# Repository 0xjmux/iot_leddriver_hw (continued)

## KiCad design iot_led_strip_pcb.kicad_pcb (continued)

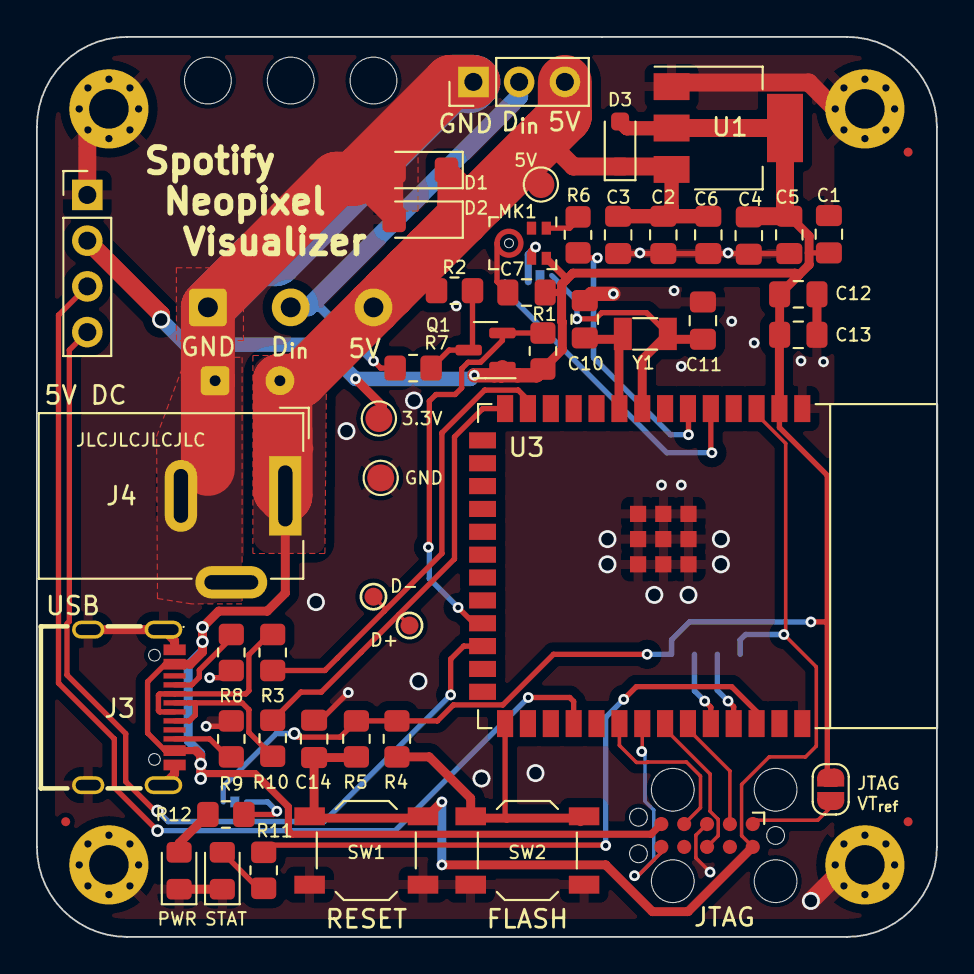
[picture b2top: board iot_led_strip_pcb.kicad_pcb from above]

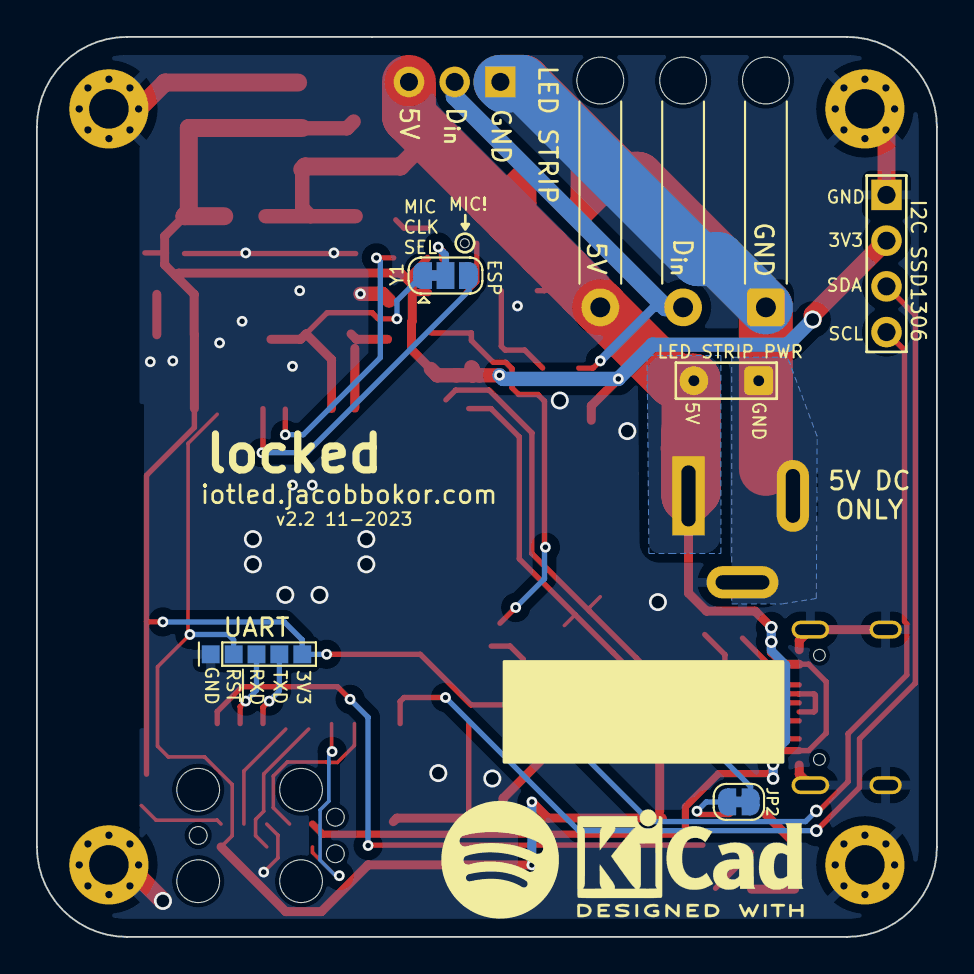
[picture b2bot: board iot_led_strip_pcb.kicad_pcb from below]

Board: 2 copper layers, 50.0 x 50.0 mm, 59 parts (4 on the bottom side), 33 nets.

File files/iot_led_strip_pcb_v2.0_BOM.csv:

"Source:","/home/jmux/Github/spotify-iot-led-driver/iot_leddriver_hw/iot_led_strip_pcb.kicad_sch"
"Date:","Sun 17 Sep 2023 01:23:37 PM PDT"
"Tool:","Eeschema 7.0.6-1.fc37"
"Generator:","/usr/share/kicad/plugins/bom_csv_grouped_by_value.py"
"Component Count:","38"

"Collated Components:"

"Item","Qty","Reference(s)","Value","LibPart","Footprint","Datasheet","DNP","LCSC","Sim.Device","Sim.Params","Sim.Pins","Sim.Type","Vendor"
"1","6","C1, C2, C3, C5, C7, C13","10uF","Device:C","Capacitor_SMD:C_0805_2012Metric_Pad1.18x1.45mm_HandSolder","~","","C15850","","","","","https://www.lcsc.com/product-detail/Multilayer-Ceramic-Capac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"
"2","3","C4, C6, C12","100nF","Device:C","Capacitor_SMD:C_0805_2012Metric_Pad1.18x1.45mm_HandSolder","~","","C49678","","","","","https://jlcpcb.com/partdetail/Yageo-CC0805KRX7R9BB104/C49678"
"3","2","C8, C9","47pF","Device:C","Capacitor_SMD:C_0805_2012Metric_Pad1.18x1.45mm_HandSolder","~","","C1804","","","","","https://www.lcsc.com/product-detail/Multilayer-Ceramic-Capac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"
"4","2","C10, C11","22pF","Device:C","Capacitor_SMD:C_0805_2012Metric_Pad1.18x1.45mm_HandSolder","~","","C1804","","","","","https://www.lcsc.com/product-detail/Multilayer-Ceramic-Capac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"
"5","2","D1, D2","SMF5V0A","Diode:SMF5V0A","Diode_SMD:D_SMF","https://www.vishay.com/doc?85881","","C1972946","","","","",""
"6","1","D3","1N5819WS","Device:D_Schottky","Diode_SMD:D_SOD-323_HandSoldering","~","","C191023","","","","",""
"7","1","D4","LED","Device:LED","LED_SMD:LED_0805_2012Metric_Pad1.15x1.40mm_HandSolder","~","","C84256","","","","","https://www.lcsc.com/product-detail/Light-Emitting-Diodes-LE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"
"8","1","D5","PWR_LED","Device:LED","LED_SMD:LED_0805_2012Metric_Pad1.15x1.40mm_HandSolder","~","","C84256","","","","","https://www.lcsc.com/product-detail/Light-Emitting-Diodes-LE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"
"9","1","J3","GT-USB-7010ASV","gt-usb_lib:GT-USB-7010ASV","footprint:USB-C-SMD_G-SWITCH_GT-USB-7010ASV","https://atta.szlcsc.com/upload/public/pdf/source/20220407/80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","","C2988369","","","","","https://www.lcsc.com/product-detail/USB-Connectors_G-Switch-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"
"10","1","J4","Barrel_Jack_Switch_Pin3Ring","Connector:Barrel_Jack_Switch_Pin3Ring","Connector_BarrelJack:BarrelJack_Wuerth_6941xx301002","~","","","V","dc=5","1=+ 2=-","DC",""
"11","1","Q1","BSS138","Transistor_FET:BSS138","Package_TO_SOT_SMD:SOT-23","https://www.onsemi.com/pub/Collateral/BSS138-D.PDF","","C358381","","","","","https://jlcpcb.com/partdetail/Foshan_Blue_RocketElec-BSS138/C358381"
"12","4","R1, R2, R4, R5","10k","Device:R_US","Resistor_SMD:R_0805_2012Metric_Pad1.20x1.40mm_HandSolder","~","","C17414","","","","","https://www.lcsc.com/product-detail/Chip-Resistor-Surface-Mo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"
"13","2","R3, R10","27R","Device:R_US","Resistor_SMD:R_0805_2012Metric_Pad1.20x1.40mm_HandSolder","~","","C27834","","","","","https://www.lcsc.com/product-detail/Chip-Resistor-Surface-Mo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"
"14","2","R6, R7","0R","Device:R_US","Resistor_SMD:R_0805_2012Metric_Pad1.20x1.40mm_HandSolder","~","","C17414","","","","","https://www.lcsc.com/product-detail/Chip-Resistor-Surface-Mo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"
"15","2","R8, R9","5.1k","Device:R_US","Resistor_SMD:R_0805_2012Metric_Pad1.20x1.40mm_HandSolder","~","","C27834","","","","","https://www.lcsc.com/product-detail/Chip-Resistor-Surface-Mo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"
"16","2","R11, R12","100","Device:R_US","Resistor_SMD:R_0805_2012Metric_Pad1.20x1.40mm_HandSolder","~","","C17408","","","","","https://jlcpcb.com/partdetail/18096-0805W8F1000T5E/C17408"
"17","1","SW1","RESET","C5117870_lib:GT-TC060A-H025-L1","Button_Switch_SMD:SW_SPST_TL3342","https://item.szlcsc.com/902766.html","","C318884","","","","","https://www.lcsc.com/product-detail/Tactile-Switches_G-Switc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"
"18","1","SW2","FLASH","C5117870_lib:GT-TC060A-H025-L1","Button_Switch_SMD:SW_SPST_TL3342","https://item.szlcsc.com/902766.html","","C318884","","","","","https://www.lcsc.com/product-detail/Tactile-Switches_G-Switc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"
"19","1","U1","AMS1117-3.3","Regulator_Linear:AMS1117-3.3","Package_TO_SOT_SMD:SOT-223-3_TabPin2","http://www.advanced-monolithic.com/pdf/ds1117.pdf","","C6186","","","","","https://www.lcsc.com/product-detail/Linear-span-style-backgr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"
"20","1","U2","ESP32-S2-MINI-1","PCM_Espressif:ESP32-S2-MINI-1","PCM_Espressif:ESP32-S2-MINI-1","https://www.espressif.com/sites/default/files/documentation/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","","C3013906","","","","",""
"21","1","Y1","Crystal_40Mhz","Device:Crystal_GND24","Crystal:Crystal_SMD_3225-4Pin_3.2x2.5mm_HandSoldering","~","","C2901712","","","","","https://jlcpcb.com/partdetail/3151525-SX3B40000F1210F30/C2901712"

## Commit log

2023-08-04 initial rev of design
2023-08-09 initial layout rev 0.1
2023-08-09 added readme and photos
2023-08-13 replaced all vias, reworked traces, DRC passes now
2023-08-13 upgrade to kicad 7, some changes to pcb text
2023-08-14 updated text, finalizing of board design, updated schematic rev number
2023-08-15 production files
2023-09-12 library changes, fixed model for dc jack
2023-09-12 modified readme, attempting verified commit
2023-09-12 testing signing
2023-09-12 some cleanup
2023-09-13 started work on new schematic
2023-09-13 schematic v1.9 initial rev
2023-09-13 some small changes to schematic, cleaned up old pcb
2023-09-13 did layout, whoops
2023-09-13 readme update
2023-09-13 renamed schematic
2023-09-13 added photos of v2 prototype and updated readme
2023-09-13 moved one thing i think
2023-09-14 some minor cleanup of schematic and layout
2023-09-16 organized schematic & added bom
2023-09-17 final modifications, cleanup, added v2.0 photos as ordered
2023-09-17 added development notes file
2023-09-26 Moved button labels and multiple minor modifications
    * Implemented Orion's suggestion for replacing 10uF cap on reset button
    with 100nF.
    * Moved silkscreen for both buttons underneath and moved jtag label.
    * Added labels to both power and status LEDs.
2023-09-29 some pcb changes and update to readme
2023-10-02 small modifications + RT render
2023-10-03 PCBA today - field edits on Cs, Rs, removed Rs on Y1
2023-10-05 modified sch to change over to esp32-s2-solo-2, should be much easier to solder
2023-10-06 board redesign around ESP32-S2-SOLO-2
2023-10-16 lots of small changes. Schematic updated with mic, layout not yet
2023-10-16 microphone added to layout, DRC passes
2023-10-16 v2.1 export, renders
2023-10-16 README updated for v2.1
2023-10-16 updated filenames and README for v2.1
2023-10-16 replaced crystal. re-updated all renders and images
2023-10-16 Update README.md v2.0 description
2023-10-16 re-re-updated photos & board
2023-10-16 readme update again
2023-10-16 re-update photo in readme
2023-10-16 updates to readme and development notes
2023-10-16 readme updates
2023-10-16 modified old version to add renders and 3D models
2023-10-16 some final readme updates, with plans to take the repo public
2023-10-18 added hardware limitations to DEV-notes
2023-10-29 some minor changes from during assembly and gif of assembled board added
2023-10-30 small readme changes, centered gif
2023-11-05 added power led disconnect and cleaned up some traces
2023-11-05 moved i2c SCL to pin on both S2 and S3
2023-11-05 label and some mini changes
2023-11-06 v2.2 as ordered
2023-11-07 added screenshots, files, updated readme for v2.2, sch & layout cleanup
2023-11-07 higher res board renders
2023-11-07 readme updates, centered images
2023-11-07 readme photos updated, centered
2023-11-09 updated readme, resized images
2023-11-14 updates to dev notes and readme
2023-11-15 added box to silkscreen for writing device name
2023-12-17 modifications before workstation change
2024-01-08 README update and addition of additional photo
    plus kicanvas link and slight reorganization of Features section
2024-01-23 added data line resistor and other small changes
2024-01-23 added case compatible with v2.0+
2024-01-23 fixing readme photo dimensions
2024-01-23 updated readme and added case readme
2024-02-23 Major schematic update for v2.3
    This was my first real PCB project, and looking back with a couple
    months of hindsight I made some mistakes. Some best practices for
    driving WS2812B strips weren't followed in my original version, and
    I've updated the schematic to reflect what I've learned and what
    improvements needed to be made.
    * Warning added to README about current version
2024-04-11 Schematic and Board redesigned for new rev: v3.0
    Schematic and board redone for next generation board - v3.0. Current rev is v3.0b.
    * pin numbers added to PCB
    * Silkscreen spot for writing board identifier in sharpie
    * Silkscreen updated with more detailed information about board and pins to improve UX
    * Logic level converters still present on data lines
    * Selectable data line resistors added
2025-02-24 v3.2 changes
    * Removed PTC fuse, since that caused issues on the last one
    * Other minor changes (that i've forgotten)
